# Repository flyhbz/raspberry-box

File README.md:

# Raspberry Box

Lever-less controller using Raspberry Pi Pico.

This project is using the following libraries. I really appreciate it!

- [ncarandini/KiCad\-RP\-Pico: A simple repository of files needed to add a 3D footprint of the Raspberry Pi Pico board to KiCad\.](https://github.com/ncarandini/KiCad-RP-Pico)
- [keebio/Keebio\-Parts\.pretty: Various KiCAD footprints for mechanical keyboard parts](https://github.com/keebio/Keebio-Parts.pretty)
- [OpenStickCommunity/GP2040\-CE](https://github.com/OpenStickCommunity/GP2040-CE)

## License

Creative Commons CC-BY-SA 4.0 License

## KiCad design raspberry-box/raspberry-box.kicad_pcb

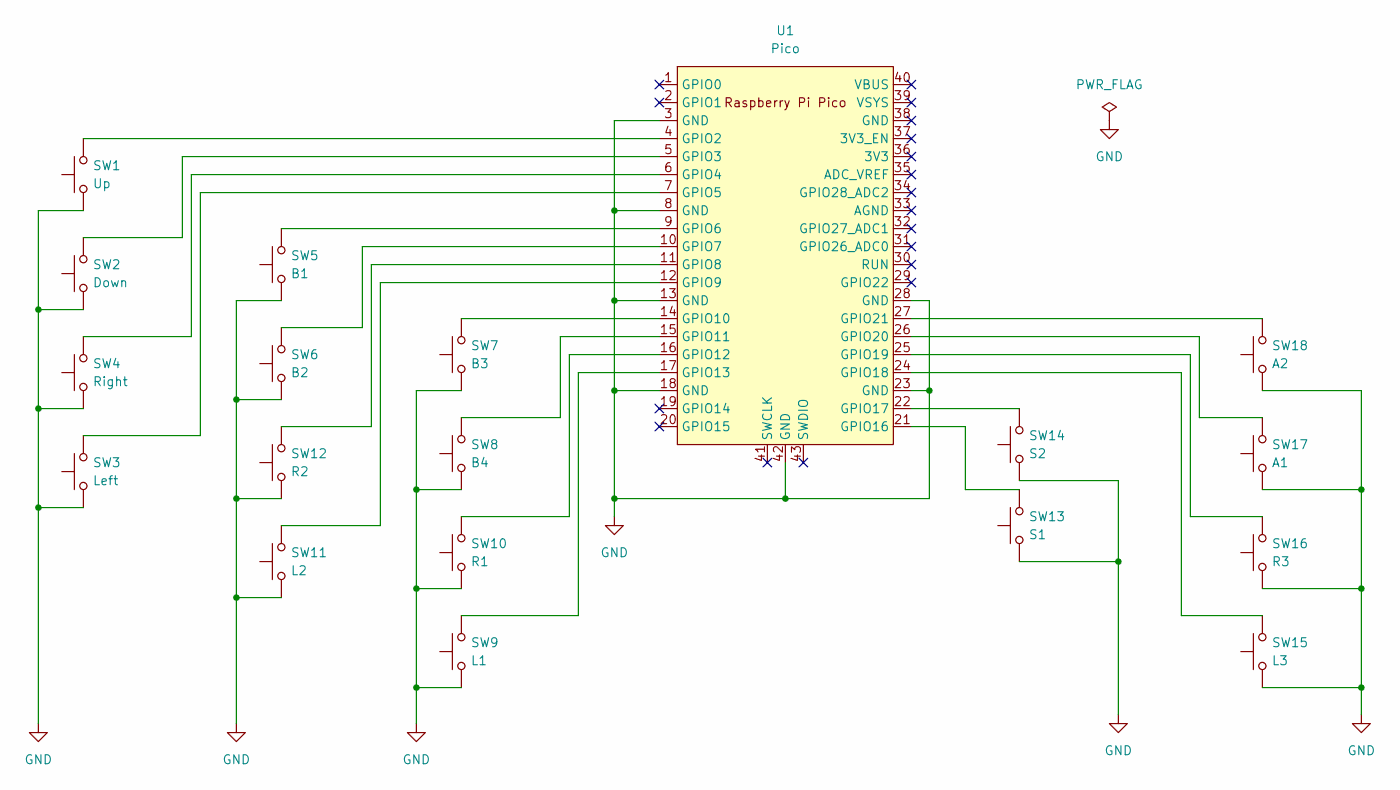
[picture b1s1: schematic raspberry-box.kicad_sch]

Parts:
SW1: Up; Cherry-MX-Low-Profile
SW2: Down; Cherry-MX-Low-Profile
SW3: Left; Cherry-MX-Low-Profile
SW4: Right; Cherry-MX-Low-Profile
SW5: B1; Cherry-MX-Low-Profile
SW6: B2; Cherry-MX-Low-Profile
SW7: B3; Cherry-MX-Low-Profile
SW8: B4; Cherry-MX-Low-Profile
SW9: L1; Cherry-MX-Low-Profile
SW10: R1; Cherry-MX-Low-Profile
SW11: L2; Cherry-MX-Low-Profile
SW12: R2; Cherry-MX-Low-Profile
SW13: S1; Cherry-MX-Low-Profile
SW14: S2; Cherry-MX-Low-Profile
SW15: L3; Cherry-MX-Low-Profile
SW16: R3; Cherry-MX-Low-Profile
SW17: A1; Cherry-MX-Low-Profile
SW18: A2; Cherry-MX-Low-Profile
U1: Pico; RPi_Pico_SMD_TH

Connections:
GND: SW1.1, SW2.1, SW3.1, SW4.1, SW5.1, SW6.1, SW7.1, SW8.1, SW9.1, SW10.1, SW11.1, SW12.1, SW13.1, SW14.1, SW15.1, SW16.1, SW17.1, SW18.1, U1.3 (GND), U1.8 (GND), U1.13 (GND), U1.18 (GND), U1.23 (GND), U1.28 (GND), U1.42 (GND)
unnamed: SW1.2, U1.4 (GPIO2)
unnamed: SW2.2, U1.5 (GPIO3)
unnamed: SW4.2, U1.6 (GPIO4)
unnamed: SW3.2, U1.7 (GPIO5)
unnamed: SW5.2, U1.9 (GPIO6)
unnamed: SW6.2, U1.10 (GPIO7)
unnamed: SW12.2, U1.11 (GPIO8)
unnamed: SW11.2, U1.12 (GPIO9)
unnamed: SW7.2, U1.14 (GPIO10)
unnamed: SW8.2, U1.15 (GPIO11)
unnamed: SW10.2, U1.16 (GPIO12)
unnamed: SW9.2, U1.17 (GPIO13)
unnamed: SW13.2, U1.21 (GPIO16)
unnamed: SW14.2, U1.22 (GPIO17)
unnamed: SW15.2, U1.24 (GPIO18)
unnamed: SW16.2, U1.25 (GPIO19)
unnamed: SW17.2, U1.26 (GPIO20)
unnamed: SW18.2, U1.27 (GPIO21)

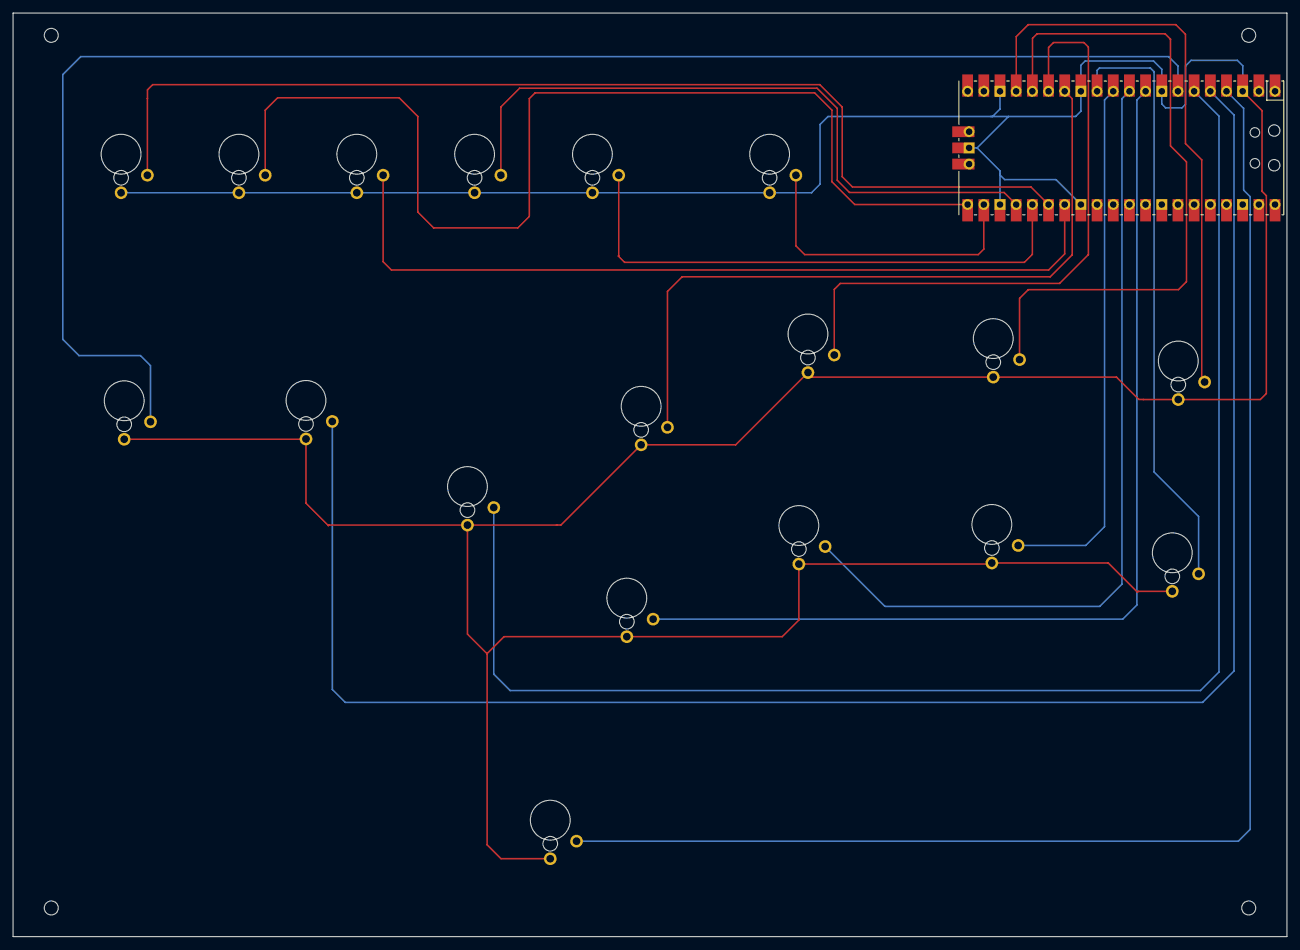
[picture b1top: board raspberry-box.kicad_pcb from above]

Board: 2 copper layers, 200.0 x 145.0 mm, 19 parts (0 on the bottom side), 19 nets.

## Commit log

2023-07-31 add kicad project
2023-07-31 add case
2023-07-31 add LICENSE
2023-07-31 add README
